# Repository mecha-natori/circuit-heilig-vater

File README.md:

# Heilig Vater

Heilig Vaterは[STM32F405RGT6]を使用した12V出力駆動用基板です。

## 仕様

|        機能         | 個数 | 備考                                            |
| :-----------------: | ---: | :---------------------------------------------- |
|         MCU         |    1 | [STM32F405RGT6]                                 |
|       ST-LINK       |    1 | ピンアサインはSWD                               |
|         CAN         |    2 | 電源ピンは5V、Classic CANのみ対応、1系統から2個 |
|   12Vデジタル出力   |   14 | インジケータLED付き                             |
|  リセットスイッチ   |    1 |                                                 |
| 5V-3.3Vレギュレータ |    1 | 外部電源からの供給用                            |
|    M.U氏の御尊顔    |    1 | 目が光る！(電源供給確認用(建前))                |
|     寸法(外形)      |      | 111mm x 86mm                                    |
|   寸法(ネジ穴間)    |      | 100mm x 75mm                                    |

## 名前の由来

**H**igh **V**oltageです。今回はひねくれてドイツ語にしてみました。\
Heilig Vater beobachtet dich.

## 使用フォント

- KiCad Font : シンボル名・部名
- Times New Roman : 右下基板名
- [UnifrakturMaguntia - Google Fonts] : 左下"Heilig Vater beobachtet dich."
- [機械彫刻用標準書体フォント] : その他テキスト

[stm32f405rgt6]: https://www.stmcu.jp/stm32/stm32f4/stm32f405415/12229
[unifrakturmaguntia - google fonts]: https://fonts.google.com/specimen/UnifrakturMaguntia
[機械彫刻用標準書体フォント]: https://font.kim

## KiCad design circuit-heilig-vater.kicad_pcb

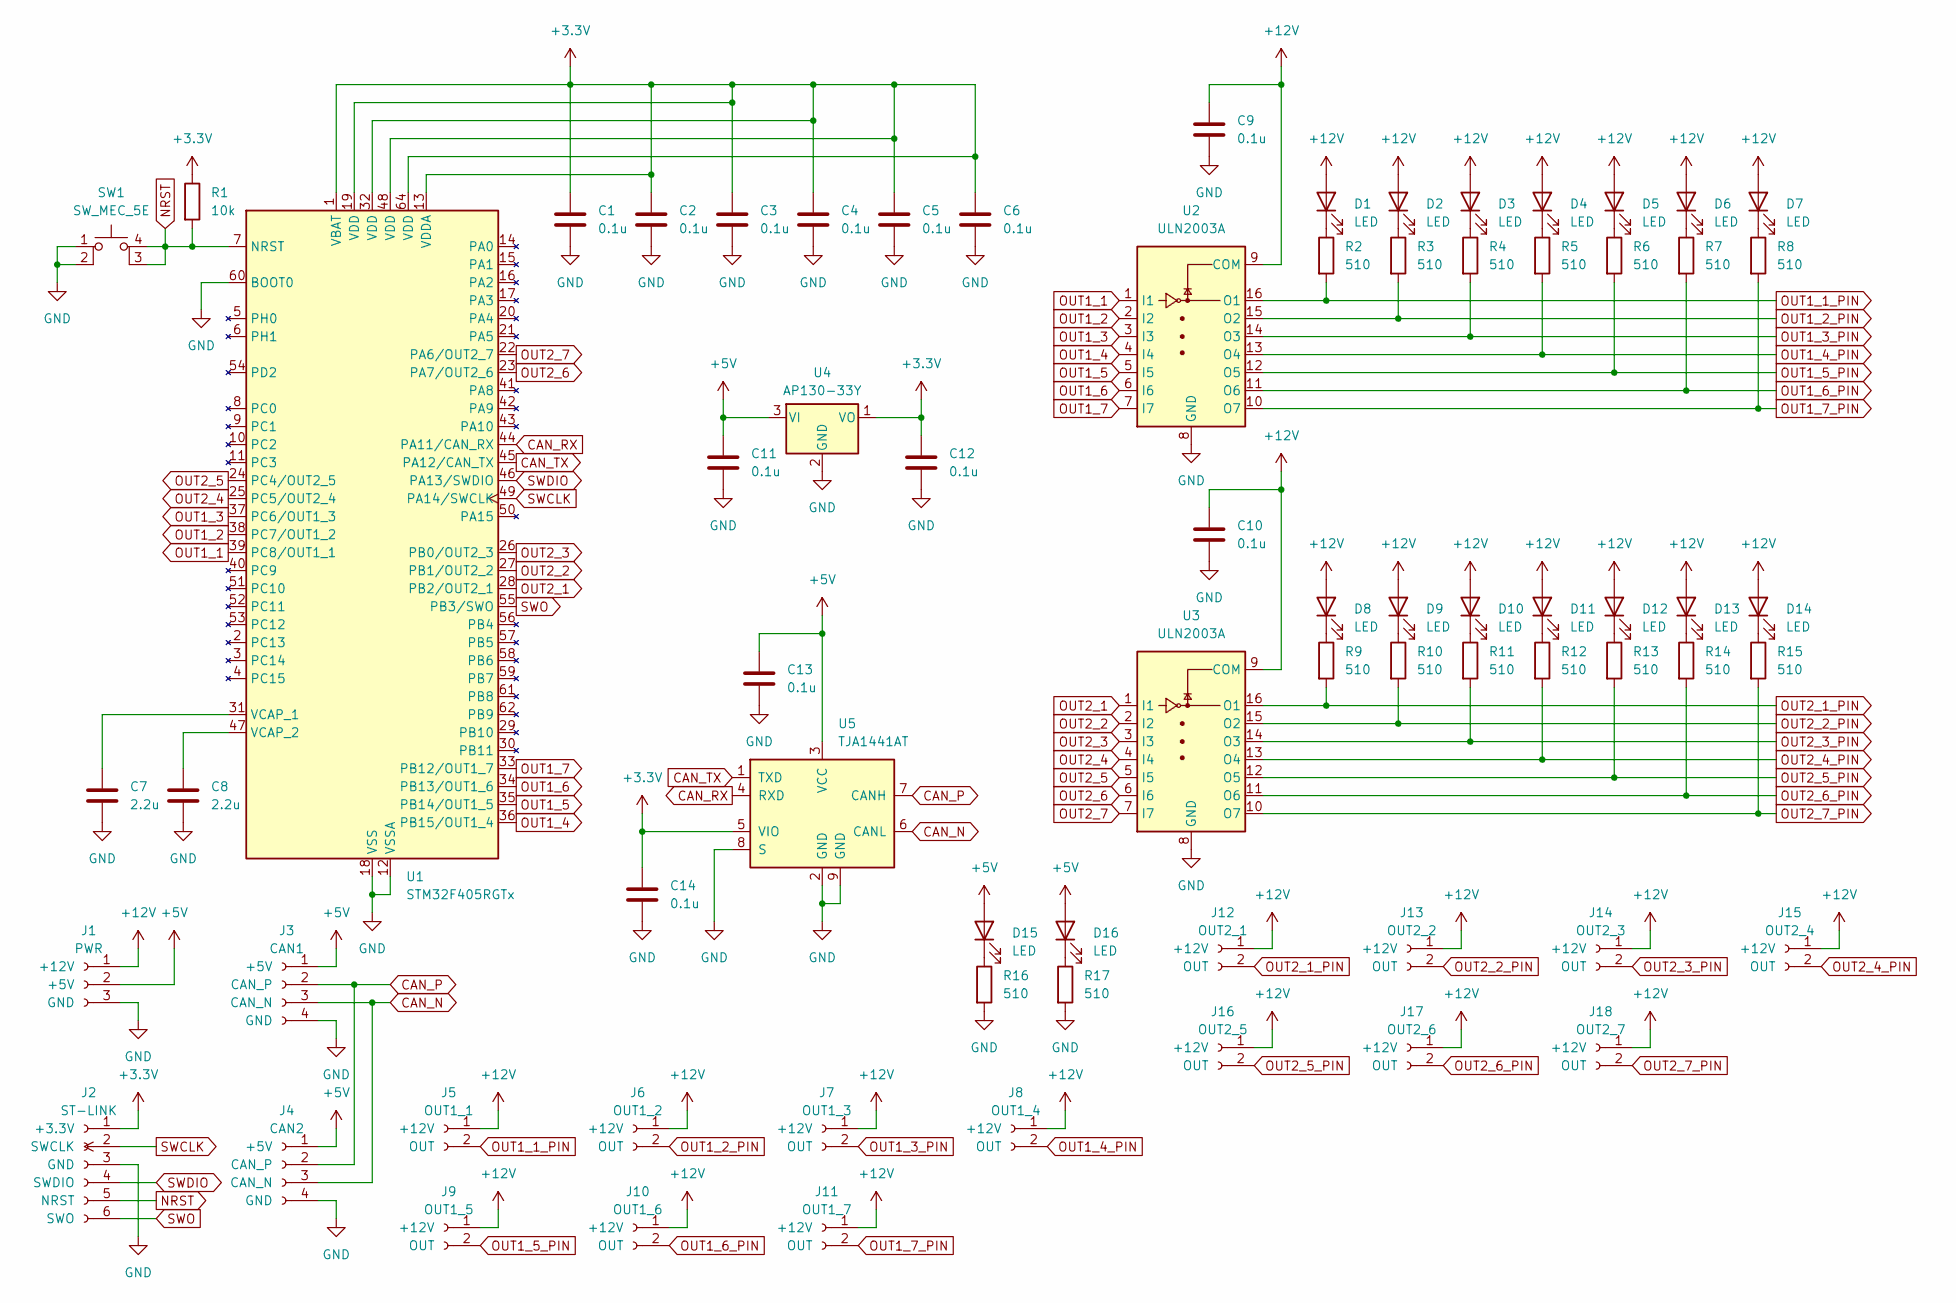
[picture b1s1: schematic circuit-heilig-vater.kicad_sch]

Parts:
C1, C2, C3, C4, C5, C6, C9, C10, C11, C12, C13, C14: 0.1u; C_0603_1608Metric_Pad1.08x0.95mm_HandSolder
C7, C8: 2.2u; C_0603_1608Metric_Pad1.08x0.95mm_HandSolder
D1, D2, D3, D4, D5, D6, D7, D8, D9, D10, D11, D12, D13, D14, D15, D16: LED; LED_0603_1608Metric_Pad1.05x0.95mm_HandSolder
J1: PWR; JST_XH_S3B-XH-A_1x03_P2.50mm_Horizontal
J2: ST-LINK; JST_ZH_B6B-ZR_1x06_P1.50mm_Vertical
J3: CAN1; JST_XA_B04B-XASK-1_1x04_P2.50mm_Vertical
J4: CAN2; JST_XA_B04B-XASK-1_1x04_P2.50mm_Vertical
J5: OUT1_1; JST_XH_B2B-XH-A_1x02_P2.50mm_Vertical
J6: OUT1_2; JST_XH_B2B-XH-A_1x02_P2.50mm_Vertical
J7: OUT1_3; JST_XH_B2B-XH-A_1x02_P2.50mm_Vertical
J8: OUT1_4; JST_XH_B2B-XH-A_1x02_P2.50mm_Vertical
J9: OUT1_5; JST_XH_B2B-XH-A_1x02_P2.50mm_Vertical
J10: OUT1_6; JST_XH_B2B-XH-A_1x02_P2.50mm_Vertical
J11: OUT1_7; JST_XH_B2B-XH-A_1x02_P2.50mm_Vertical
J12: OUT2_1; JST_XH_B2B-XH-A_1x02_P2.50mm_Vertical
J13: OUT2_2; JST_XH_B2B-XH-A_1x02_P2.50mm_Vertical
J14: OUT2_3; JST_XH_B2B-XH-A_1x02_P2.50mm_Vertical
J15: OUT2_4; JST_XH_B2B-XH-A_1x02_P2.50mm_Vertical
J16: OUT2_5; JST_XH_B2B-XH-A_1x02_P2.50mm_Vertical
J17: OUT2_6; JST_XH_B2B-XH-A_1x02_P2.50mm_Vertical
J18: OUT2_7; JST_XH_B2B-XH-A_1x02_P2.50mm_Vertical
R1: 10k; R_0603_1608Metric_Pad0.98x0.95mm_HandSolder
R2, R3, R4, R5, R6, R7, R8, R9, R10, R11, R12, R13, R14, R15, R16, R17: 510; R_0603_1608Metric_Pad0.98x0.95mm_HandSolder
SW1: SW_MEC_5E; tact
U1: STM32F405RGTx; LQFP-64_10x10mm_P0.5mm
U2, U3: ULN2003A; DIP-16_W7.62mm_LongPads
U4: AP130-33Y; SOT-89-3
U5: TJA1441AT; SOIC-8-1EP_3.9x4.9mm_P1.27mm_EP2.41x3.81mm_ThermalVias

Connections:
+3.3V: C1.1, C2.1, C3.1, C4.1, C5.1, C6.1, C12.1, C14.1, J2.1 (+3.3V), R1.1, U1.1 (VBAT), U1.13 (VDDA), U1.19 (VDD), U1.32 (VDD), U1.48 (VDD), U1.64 (VDD), U4.1 (VO), U5.5 (VIO)
+5V: C11.1, C13.1, D15.2 (A), D16.2 (A), J1.2 (+5V), J3.1 (+5V), J4.1 (+5V), U4.3 (VI), U5.3 (VCC)
+12V: C9.1, C10.1, D1.2 (A), D2.2 (A), D3.2 (A), D4.2 (A), D5.2 (A), D6.2 (A), D7.2 (A), D8.2 (A), D9.2 (A), D10.2 (A), D11.2 (A), D12.2 (A), D13.2 (A), D14.2 (A), J1.1 (+12V), J5.1 (+12V), J6.1 (+12V), J7.1 (+12V), J8.1 (+12V), J9.1 (+12V), J10.1 (+12V), J11.1 (+12V), J12.1 (+12V), J13.1 (+12V), J14.1 (+12V), J15.1 (+12V), J16.1 (+12V), J17.1 (+12V), J18.1 (+12V), U2.9 (COM), U3.9 (COM)
CAN_N: J3.3 (CAN_N), J4.3 (CAN_N), U5.6 (CANL)
CAN_P: J3.2 (CAN_P), J4.2 (CAN_P), U5.7 (CANH)
CAN_RX: U1.44 (PA11/CAN_RX), U5.4 (RXD)
CAN_TX: U1.45 (PA12/CAN_TX), U5.1 (TXD)
GND: C1.2, C2.2, C3.2, C4.2, C5.2, C6.2, C7.2, C8.2, C9.2, C10.2, C11.2, C12.2, C13.2, C14.2, J1.3 (GND), J2.3 (GND), J3.4 (GND), J4.4 (GND), R16.2, R17.2, SW1.1, SW1.2, U1.12 (VSSA), U1.18 (VSS), U1.60 (BOOT0), U1.63 (VSS), U2.8 (GND), U3.8 (GND), U4.2 (GND), U5.2 (GND), U5.8 (S), U5.9 (GND)
NRST: J2.5 (NRST), R1.2, SW1.3 (K), SW1.4 (A), U1.7 (NRST)
unnamed: D1.1 (K), R2.1
unnamed: D2.1 (K), R3.1
unnamed: D3.1 (K), R4.1
unnamed: D4.1 (K), R5.1
unnamed: D5.1 (K), R6.1
unnamed: D6.1 (K), R7.1
unnamed: D7.1 (K), R8.1
unnamed: D8.1 (K), R9.1
unnamed: D9.1 (K), R10.1
unnamed: D10.1 (K), R11.1
unnamed: D11.1 (K), R12.1
unnamed: D12.1 (K), R13.1
unnamed: D13.1 (K), R14.1
unnamed: D14.1 (K), R15.1
unnamed: D15.1 (K), R16.1
unnamed: D16.1 (K), R17.1
unnamed: C7.1, U1.31 (VCAP_1)
unnamed: C8.1, U1.47 (VCAP_2)
OUT1_1: U1.39 (PC8/OUT1_1), U2.1 (I1)
OUT1_1_PIN: J5.2 (OUT), R2.2, U2.16 (O1)
OUT1_2: U1.38 (PC7/OUT1_2), U2.2 (I2)
OUT1_2_PIN: J6.2 (OUT), R3.2, U2.15 (O2)
OUT1_3: U1.37 (PC6/OUT1_3), U2.3 (I3)
OUT1_3_PIN: J7.2 (OUT), R4.2, U2.14 (O3)
OUT1_4: U1.36 (PB15/OUT1_4), U2.4 (I4)
OUT1_4_PIN: J8.2 (OUT), R5.2, U2.13 (O4)
OUT1_5: U1.35 (PB14/OUT1_5), U2.5 (I5)
OUT1_5_PIN: J9.2 (OUT), R6.2, U2.12 (O5)
OUT1_6: U1.34 (PB13/OUT1_6), U2.6 (I6)
OUT1_6_PIN: J10.2 (OUT), R7.2, U2.11 (O6)
OUT1_7: U1.33 (PB12/OUT1_7), U2.7 (I7)
OUT1_7_PIN: J11.2 (OUT), R8.2, U2.10 (O7)
OUT2_1: U1.28 (PB2/OUT2_1), U3.1 (I1)
OUT2_1_PIN: J12.2 (OUT), R9.2, U3.16 (O1)
OUT2_2: U1.27 (PB1/OUT2_2), U3.2 (I2)
OUT2_2_PIN: J13.2 (OUT), R10.2, U3.15 (O2)
OUT2_3: U1.26 (PB0/OUT2_3), U3.3 (I3)
OUT2_3_PIN: J14.2 (OUT), R11.2, U3.14 (O3)
OUT2_4: U1.25 (PC5/OUT2_4), U3.4 (I4)
OUT2_4_PIN: J15.2 (OUT), R12.2, U3.13 (O4)
OUT2_5: U1.24 (PC4/OUT2_5), U3.5 (I5)
OUT2_5_PIN: J16.2 (OUT), R13.2, U3.12 (O5)
OUT2_6: U1.23 (PA7/OUT2_6), U3.6 (I6)
OUT2_6_PIN: J17.2 (OUT), R14.2, U3.11 (O6)
OUT2_7: U1.22 (PA6/OUT2_7), U3.7 (I7)
OUT2_7_PIN: J18.2 (OUT), R15.2, U3.10 (O7)
SWCLK: J2.2 (SWCLK), U1.49 (PA14/SWCLK)
SWDIO: J2.4 (SWDIO), U1.46 (PA13/SWDIO)
SWO: J2.6 (SWO), U1.55 (PB3/SWO)

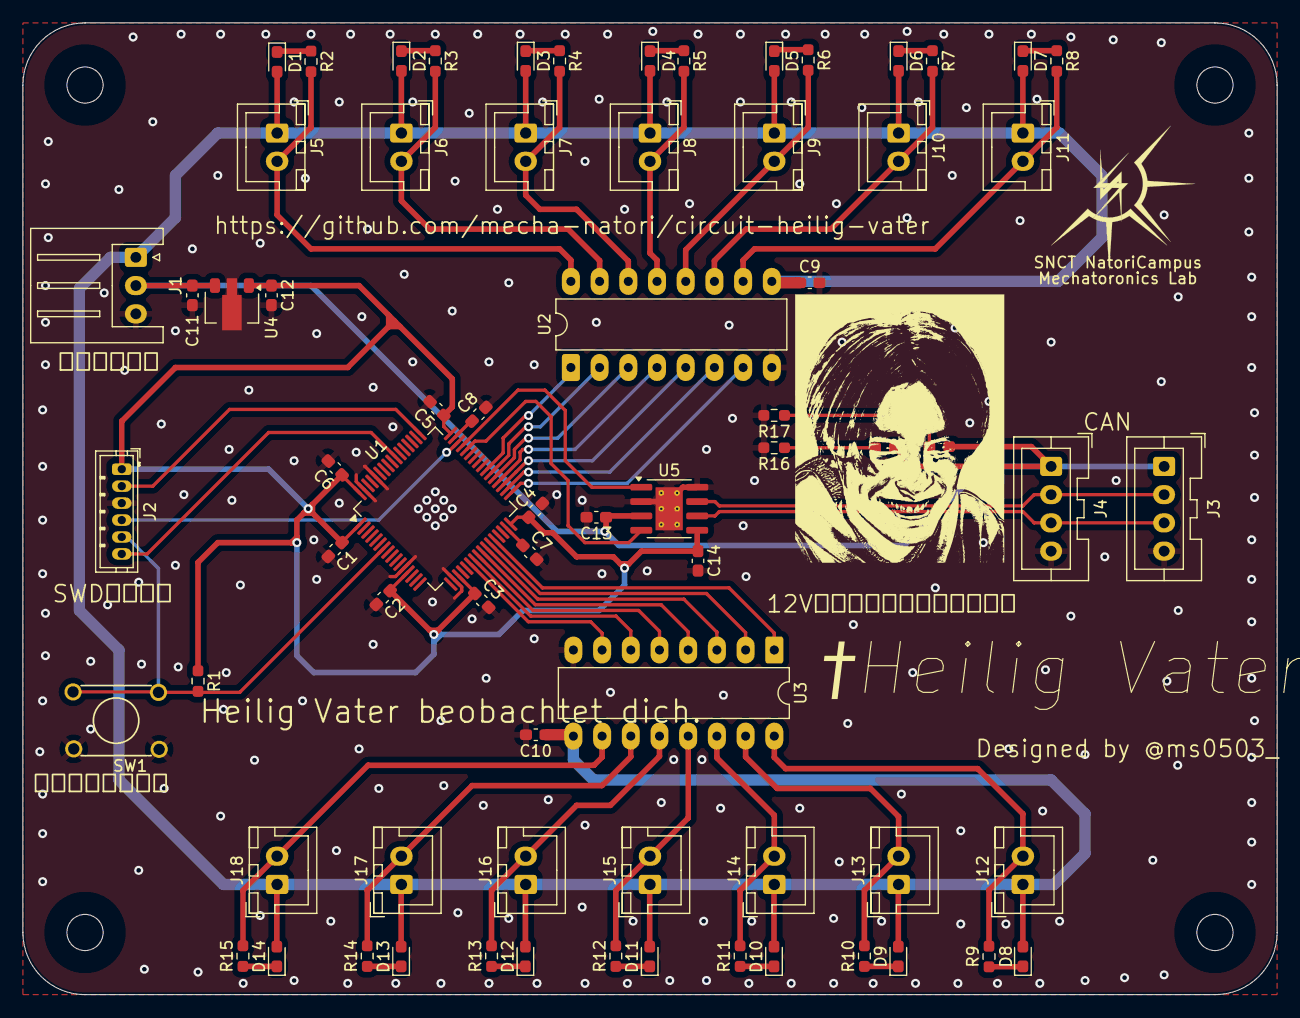
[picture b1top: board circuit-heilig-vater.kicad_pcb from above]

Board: 2 copper layers, 111.0 x 86.0 mm, 75 parts (0 on the bottom side), 58 nets.

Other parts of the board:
 : holeφ3.2
 #2,  #3,  #4: holeφ3.2

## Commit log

2025-06-16 feature: 回路図PDFを追加。
